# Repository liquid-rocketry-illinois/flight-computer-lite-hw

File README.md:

# Flight Computer Lite "Digital Tripper"
KiCad PCB repository for "Digital Tripper": a flight computer with no physical outputs designed for uncontrolled solid-fuel excursion flights (the first of which is planned for 2024-11), and a precursor for future flight computers that will incorporate actuation or active control or interact with other boards. The data it gathers will be used for verification of flight control and position estimation algorithms, flight vehicle design iteration, building up a strong avionics software backbone, and field-testing our electronic components and designs. Digital Tripper is a square 65mm on edge and fits transversely in a 4-inch-diameter model rocket.

Ingredients:
* The "brain", a Raspberry Pi Silicon RP2040
* Various digital sensors
    * TDK InvenSense ICM-42688-P high-accuracy 6DoF IMU
    * Bosch BMI088 6DoF IMU for backup and a higher (24 g) acceleration limit
    * STmicroelectronics LIS3MDL 3-axis magnetometer
    * TE Connectivity MS5611 barometer/altimeter
    * Sensirion SHT40 for ambient temperature and humidity
    * u-blox MAX-M10S GNSS receiver with u.FL antenna
* A push-push microSD card slot for vibration-resistant datalogging
* A piezoelectric buzzer to provide audial status information before launch and after landing
* a USB-C port for programming and serial communication with the RP2040
* A JST-PH battery connector
* Power monitor IC to characterize necessary battery size
* A 3.3V-output switching DC-DC converter

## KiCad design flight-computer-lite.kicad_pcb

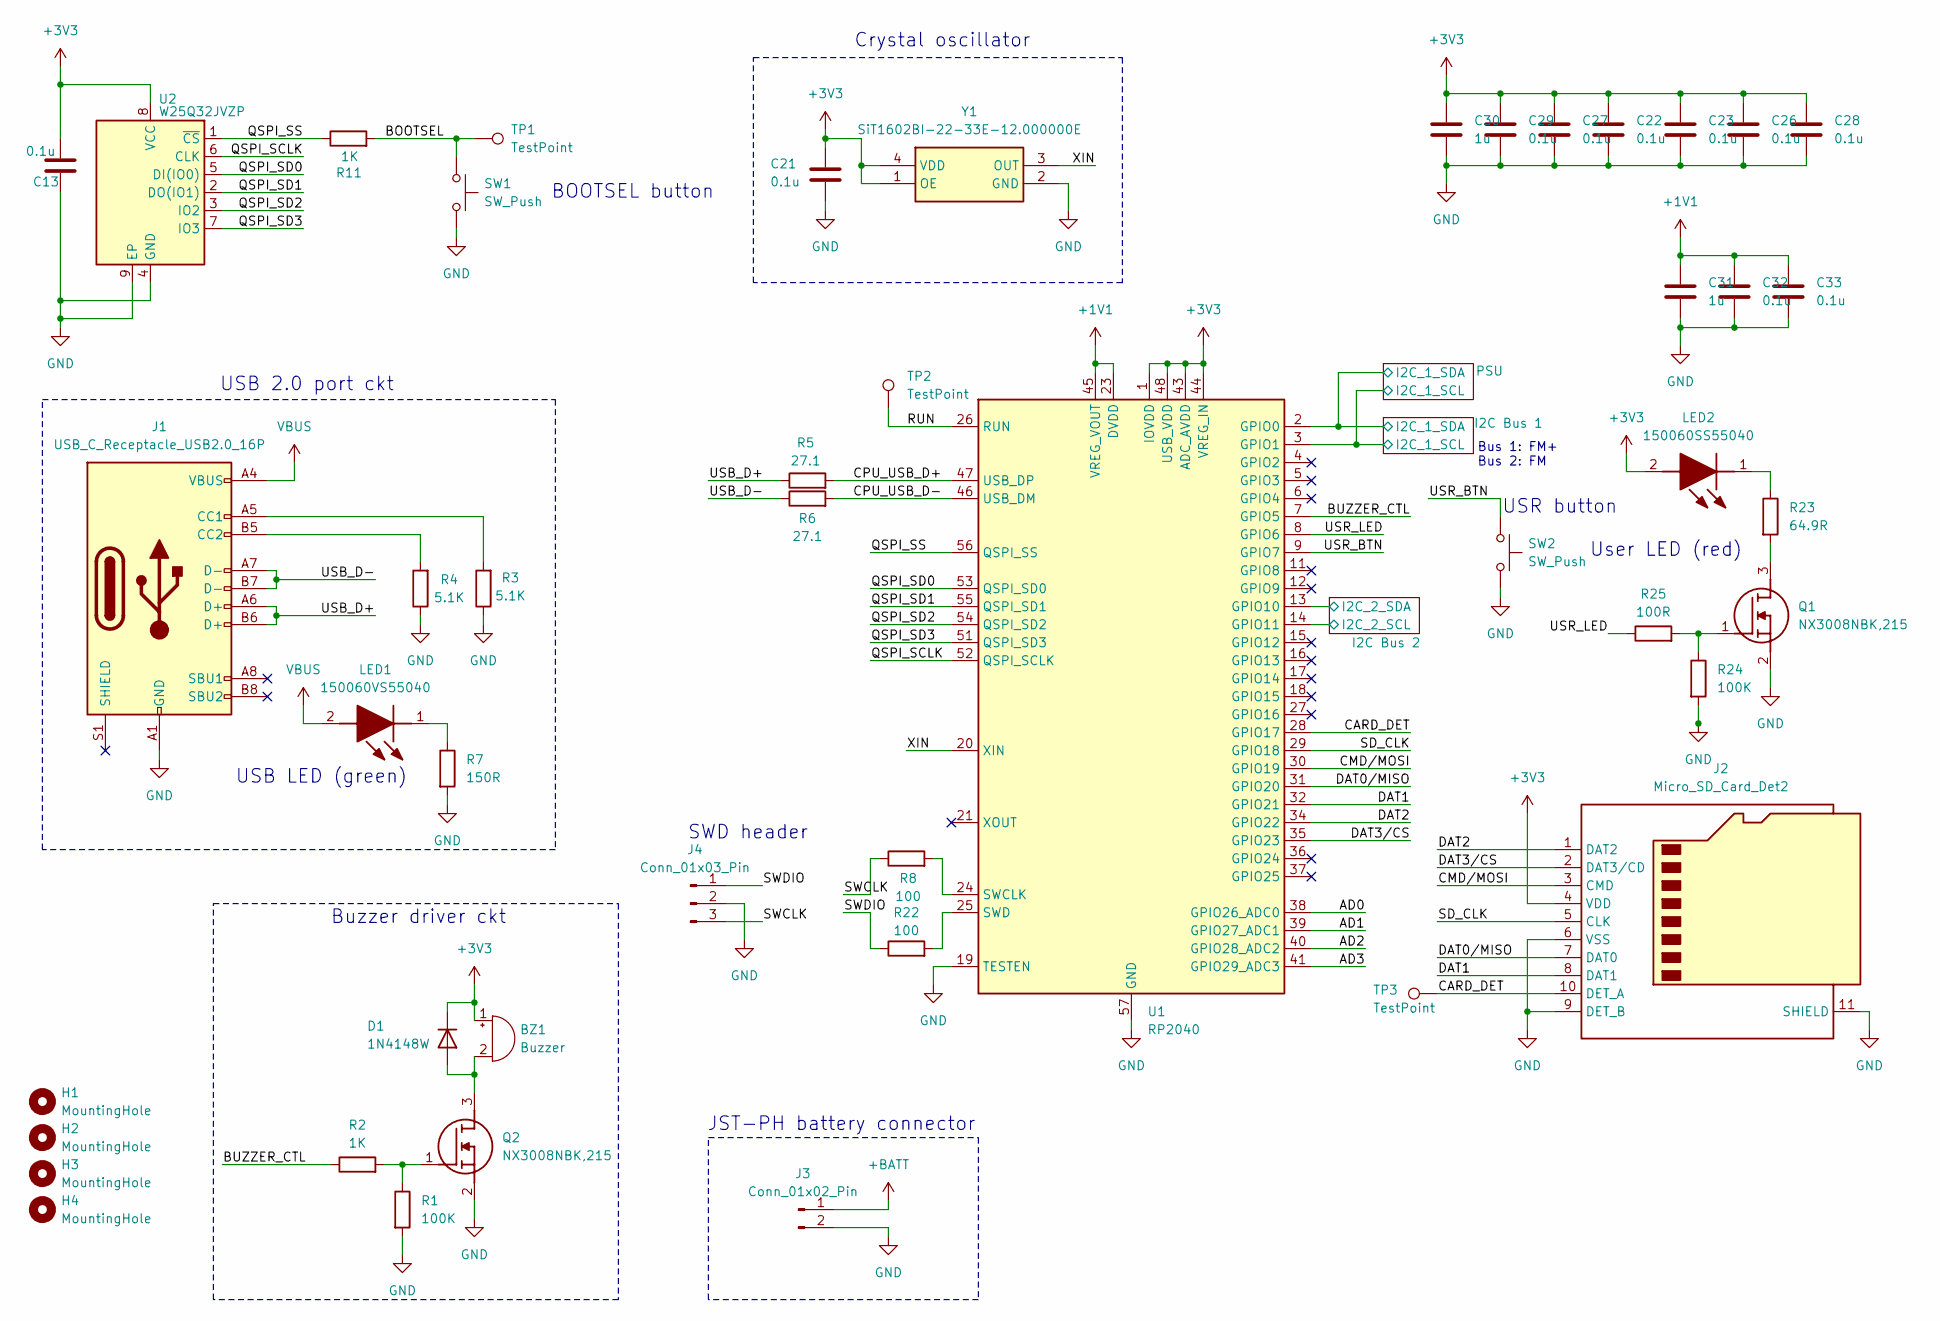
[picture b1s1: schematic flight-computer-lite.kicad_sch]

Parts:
BZ1: Buzzer; MagneticBuzzer_PUI_SMT-1028-T-2-R
C13, C21, C22, C23, C26, C27, C28, C29, C32, C33: 0.1u; C_0603_1608Metric
C30, C31: 1u; C_0603_1608Metric
D1: 1N4148W; D_SOD-323F
H1, H2, H3, H4: MountingHole; MountingHole_4.3mm_M4
J1: USB_C_Receptacle_USB2.0_16P; USB_C_Receptacle_GCT_USB4110
J2: Micro_SD_Card_Det2; microSD_HC_Hirose_DM3AT-SF-PEJM5
J3: Conn_01x02_Pin; JST_PH_S2B-PH-SM4-TB_1x02-1MP_P2.00mm_Horizontal
J4: Conn_01x03_Pin; JST_SH_BM03B-SRSS-TB_1x03-1MP_P1.00mm_Vertical
LED1: 150060VS55040; LEDM168X50N; Mouser Part Number 710-150060VS55040
LED2: 150060SS55040; Mouser Part Number 710-150060SS55040
Q1, Q2: NX3008NBK,215; NX3008NBK215; Mouser Part Number 771-NX3008NBK,215
R1, R24: 100K; R_0603_1608Metric
R2, R11: 1K; R_0603_1608Metric
R3, R4: 5.1K; R_0603_1608Metric
R5, R6: 27.1; R_0603_1608Metric
R7: 150R; R_0603_1608Metric
R8, R22: 100; R_0603_1608Metric
R23: 64.9R; R_0603_1608Metric
R25: 100R; R_0603_1608Metric
SW1, SW2: SW_Push; SW_Push_1P1T_NO_Vertical_Wuerth_434133025816
TP1, TP2, TP3: TestPoint; TestPoint_Pad_D1.0mm
U1: RP2040; QFN-56-1EP_7x7mm_P0.4mm_EP3.2x3.2mm
U2: W25Q32JVZP; WSON-8-1EP_6x5mm_P1.27mm_EP3.4x4.3mm
Y1: SiT1602BI-22-33E-12.000000E; SIT1602BI2233E12000000G; Manufacturer_Part_Number SiT1602BI-22-33E-12.000000E; Mouser Part Number N/A

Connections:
+1V1: C31.1, C32.1, C33.1, U1.23 (DVDD), U1.45 (VREG_VOUT), U1.50 (DVDD)
+3V3: BZ1.1 (+), C13.1, C21.1, C22.1, C23.1, C26.1, C27.1, C28.1, C29.1, C30.1, D1.1 (K), J2.4 (VDD), LED2.2 (A), U1.1 (IOVDD), U1.10 (IOVDD), U1.22 (IOVDD), U1.33 (IOVDD), U1.42 (IOVDD), U1.43 (ADC_AVDD), U1.44 (VREG_IN), U1.48 (USB_VDD), U1.49 (IOVDD), U2.8 (VCC), Y1.1 (OE), Y1.4 (VDD); also elsewhere on the board
+BATT: J3.1; also elsewhere on the board
/AD0: U1.38 (GPIO26_ADC0)
/AD1: U1.39 (GPIO27_ADC1)
/AD2: U1.40 (GPIO28_ADC2)
/AD3: U1.41 (GPIO29_ADC3)
/BOOTSEL: R11.2, SW1.1, TP1.1
/BUZZER_CTL: R2.1, U1.7 (GPIO5)
/CARD_DET: J2.10 (DET_A), TP3.1, U1.28 (GPIO17)
/CMD/MOSI: J2.3 (CMD), U1.30 (GPIO19)
/CPU_USB_D+: R5.2, U1.47 (USB_DP)
/CPU_USB_D-: R6.2, U1.46 (USB_DM)
/DAT0/MISO: J2.7 (DAT0), U1.31 (GPIO20)
/DAT1: J2.8 (DAT1), U1.32 (GPIO21)
/DAT2: J2.1 (DAT2), U1.34 (GPIO22)
/DAT3/CS: J2.2 (DAT3/CD), U1.35 (GPIO23)
/I2C Bus 1/I2C_1_SCL: U1.3 (GPIO1); also elsewhere on the board
/I2C Bus 1/I2C_1_SDA: U1.2 (GPIO0); also elsewhere on the board
/I2C Bus 2/I2C_2_SCL: U1.14 (GPIO11); also elsewhere on the board
/I2C Bus 2/I2C_2_SDA: U1.13 (GPIO10); also elsewhere on the board
/QSPI_SCLK: U1.52 (QSPI_SCLK), U2.6 (CLK)
/QSPI_SD0: U1.53 (QSPI_SD0), U2.5 (DI(IO0))
/QSPI_SD1: U1.55 (QSPI_SD1), U2.2 (DO(IO1))
/QSPI_SD2: U1.54 (QSPI_SD2), U2.3 (IO2)
/QSPI_SD3: U1.51 (QSPI_SD3), U2.7 (IO3)
/QSPI_SS: R11.1, U1.56 (QSPI_SS), U2.1 (~CS)
/RUN: TP2.1, U1.26 (RUN)
/SD_CLK: J2.5 (CLK), U1.29 (GPIO18)
/SWCLK: J4.3, R8.1
/SWDIO: J4.1, R22.1
/USB_D+: J1.A6 (D+), J1.B6 (D+), R5.1
/USB_D-: J1.A7 (D-), J1.B7 (D-), R6.1
/USR_BTN: SW2.1, U1.9 (GPIO7)
/USR_LED: R25.1, U1.8 (GPIO6)
/XIN: U1.20 (XIN), Y1.3 (OUT)
GND: C13.2, C21.2, C22.2, C23.2, C26.2, C27.2, C28.2, C29.2, C30.2, C31.2, C32.2, C33.2, J1.A1 (GND), J1.A12 (GND), J1.B1 (GND), J1.B12 (GND), J2.6 (VSS), J2.9 (DET_B), J2.11 (SHIELD), J3.2, J4.2, J4.MP, Q1.2 (S), Q2.2 (S), R1.2, R3.1, R4.1, R7.2, R24.2, SW1.2, SW2.2, U1.19 (TESTEN), U1.57 (GND), U2.4 (GND), U2.9 (EP), Y1.2 (GND); also elsewhere on the board
unnamed: BZ1.2 (-), D1.2 (A), Q2.3 (D)
unnamed: J1.A5 (CC1), R3.2
unnamed: J1.B5 (CC2), R4.2
unnamed: LED1.1 (K), R7.1
unnamed: LED2.1 (K), R23.1
unnamed: Q1.3 (D), R23.2
unnamed: Q1.1 (G), R24.1, R25.2
unnamed: Q2.1 (G), R1.1, R2.2
unnamed: R8.2, U1.24 (SWCLK)
unnamed: R22.2, U1.25 (SWD)
VBUS: J1.A4 (VBUS), J1.A9 (VBUS), J1.B4 (VBUS), J1.B9 (VBUS), LED1.2 (A); also elsewhere on the board

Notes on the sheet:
Bus 1: FM+ Bus 2: FM
Buzzer driver ckt
JST-PH battery connector
BOOTSEL button
User LED (red)
SWD header
USB LED (green)
USR button
Crystal oscillator
USB 2.0 port ckt

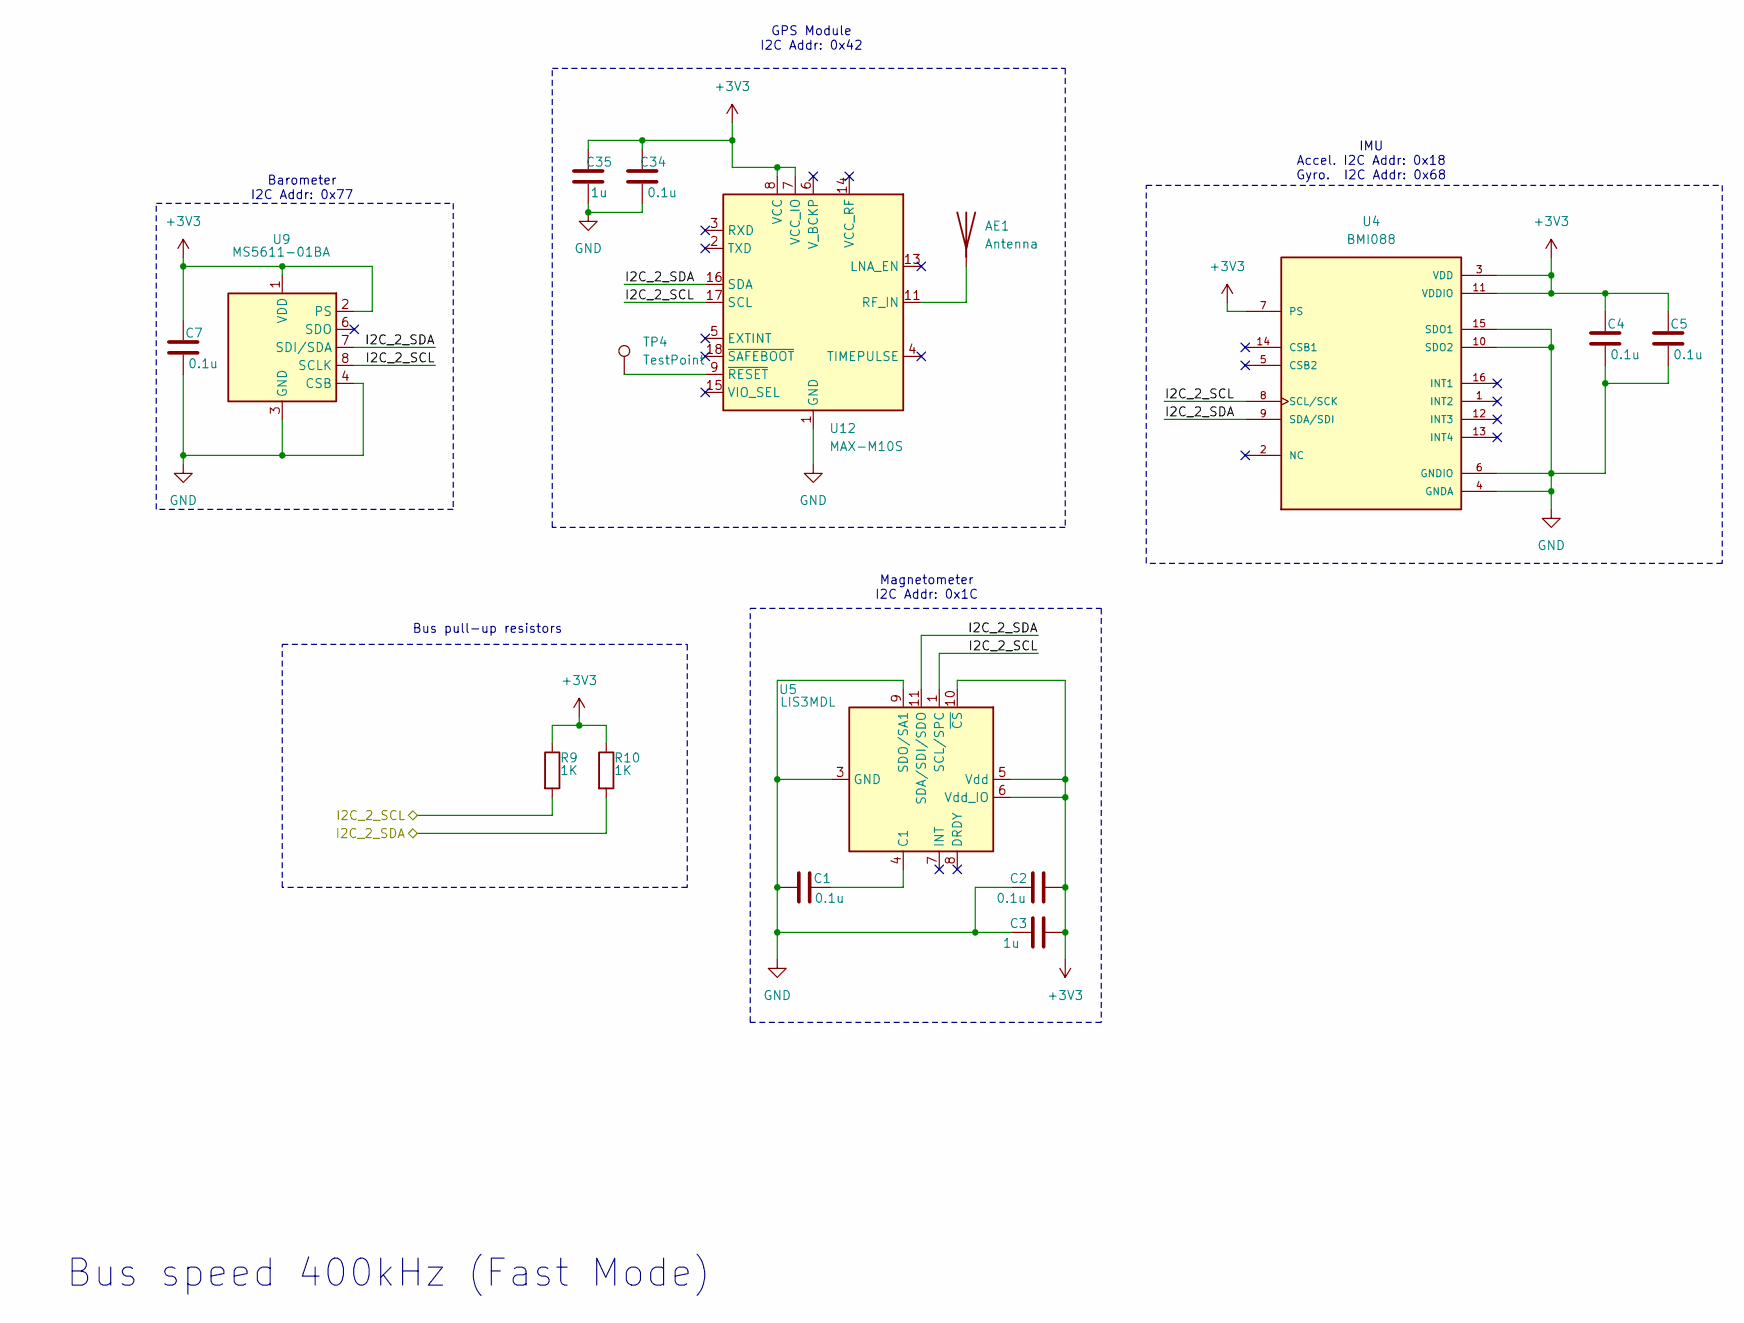
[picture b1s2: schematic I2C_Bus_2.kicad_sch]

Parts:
AE1: Antenna; U.FL_Hirose_U.FL-R-SMT-1_Vertical
C1, C2, C4, C5, C7, C34: 0.1u; C_0603_1608Metric
C3, C35: 1u; C_0603_1608Metric
R9, R10: 1K; R_0603_1608Metric
TP4: TestPoint; TestPoint_Pad_D1.0mm
U4: BMI088; PQFN50P450X300X100-16N
U5: LIS3MDL; LGA-12_2x2mm_P0.5mm
U9: MS5611-01BA; LGA-8_3x5mm_P1.25mm
U12: MAX-M10S; ublox_MAX

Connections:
+3V3: C2.2, C3.2, C4.2, C5.2, C7.2, C34.2, C35.2, R9.1, R10.1, U4.3 (VDD), U4.7 (PS), U4.11 (VDDIO), U5.5 (Vdd), U5.6 (Vdd_IO), U5.10 (~CS), U9.1 (VDD), U9.2 (PS), U12.7 (VCC_IO), U12.8 (VCC); also elsewhere on the board
/I2C Bus 2/I2C_2_SCL: R9.2, U4.8 (SCL/SCK), U5.1 (SCL/SPC), U9.8 (SCLK), U12.17 (SCL); also elsewhere on the board
/I2C Bus 2/I2C_2_SDA: R10.2, U4.9 (SDA/SDI), U5.11 (SDA/SDI/SDO), U9.7 (SDI/SDA), U12.16 (SDA); also elsewhere on the board
GND: AE1.2, C1.1, C2.1, C3.1, C4.1, C5.1, C7.1, C34.1, C35.1, U4.4 (GNDA), U4.6 (GNDIO), U4.10 (SDO2), U4.15 (SDO1), U5.2 (GND), U5.3 (GND), U5.9 (SDO/SA1), U5.12 (GND), U9.3 (GND), U9.4 (CSB), U9.5 (CSB), U12.1 (GND), U12.10 (GND), U12.12 (GND); also elsewhere on the board
unnamed: AE1.1 (A), U12.11 (RF_IN)
unnamed: C1.2, U5.4 (C1)
unnamed: TP4.1, U12.9 (~RESET)

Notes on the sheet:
Magnetometer I2C Addr: 0x1C
IMU Accel. I2C Addr: 0x18 Gyro. I2C Addr: 0x68
GPS Module I2C Addr: 0x42
Bus pull-up resistors
Bus speed 400kHz (Fast Mode)
Barometer I2C Addr: 0x77

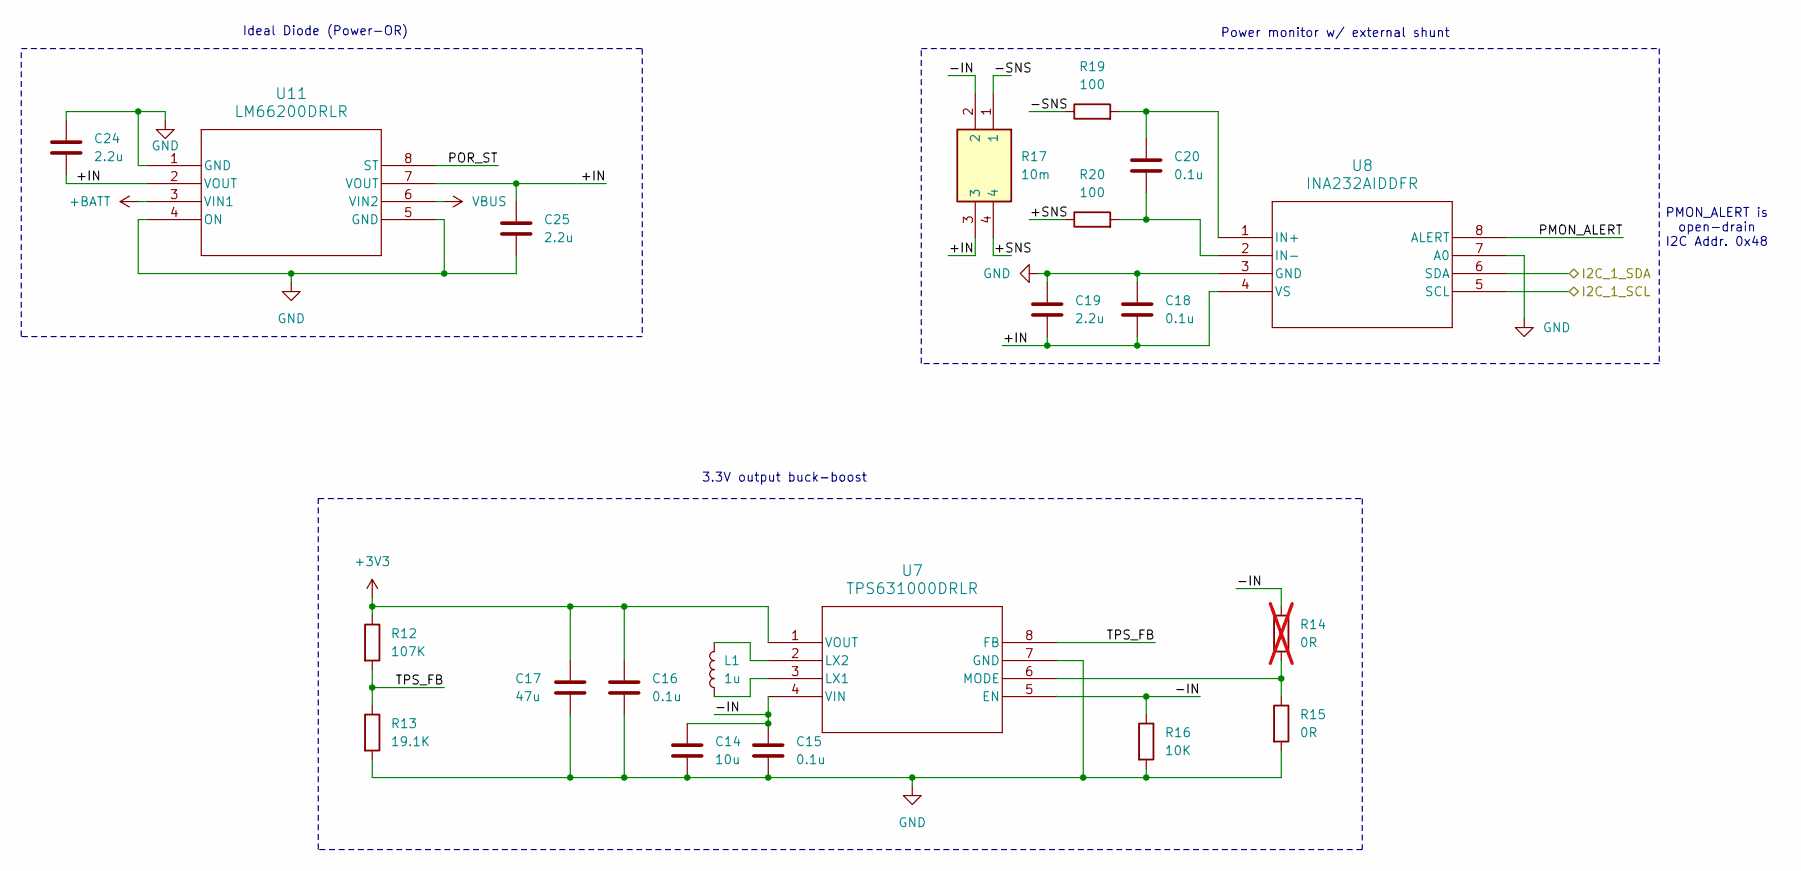
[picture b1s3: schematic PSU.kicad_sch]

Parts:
C14: 10u; C_0603_1608Metric
C15, C16, C18, C20: 0.1u; C_0603_1608Metric
C17: 47u; C_0805_2012Metric
C19, C24, C25: 2.2u; C_0603_1608Metric
L1: 1u; L_1008_2520Metric
R12: 107K; R_0603_1608Metric
R13: 19.1K; R_0603_1608Metric
R14: 0R; R_0603_1608Metric; not fitted
R15: 0R; R_0603_1608Metric
R16: 10K; R_0603_1608Metric
R17: 10m; L4CA0612L0M50FNR; Manufacturer_Part_Number L4CA0612LR010FNR
R19, R20: 100; R_0603_1608Metric
U7: TPS631000DRLR; TPS631000DRLR_TEX
U8: INA232AIDDFR
U11: LM66200DRLR; LM66200

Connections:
+3V3: C16.1, C17.1, R12.1, U7.1 (VOUT); also elsewhere on the board
+BATT: U11.3 (VIN1); also elsewhere on the board
/I2C Bus 1/I2C_1_SCL: U8.5 (SCL); also elsewhere on the board
/I2C Bus 1/I2C_1_SDA: U8.6 (SDA); also elsewhere on the board
/PSU/+IN: C18.2, C19.2, C24.2, C25.1, R17.3, U8.4 (VS), U11.2 (VOUT), U11.7 (VOUT)
/PSU/+SNS: R17.4, R20.1
/PSU/-IN: C14.1, C15.1, R14.1, R16.1, R17.2, U7.4 (VIN), U7.5 (EN)
/PSU/-SNS: R17.1, R19.1
/PSU/PMON_ALERT: U8.8 (ALERT)
/PSU/POR_ST: U11.8 (ST)
/PSU/TPS_FB: R12.2, R13.1, U7.8 (FB)
GND: C14.2, C15.2, C16.2, C17.2, C18.1, C19.1, C24.1, C25.2, R13.2, R15.2, R16.2, U7.7 (GND), U8.3 (GND), U8.7 (A0), U11.1 (GND), U11.4 (ON), U11.5 (GND); also elsewhere on the board
unnamed: L1.1, U7.3 (LX1)
unnamed: L1.2, U7.2 (LX2)
unnamed: R14.2, R15.1, U7.6 (MODE)
unnamed: C20.1, R19.2, U8.1 (IN+)
unnamed: C20.2, R20.2, U8.2 (IN-)
VBUS: U11.6 (VIN2); also elsewhere on the board

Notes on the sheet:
Power monitor w/ external shunt
PMON_ALERT is open-drain I2C Addr. 0x48
3.3V output buck-boost
Ideal Diode (Power-OR)

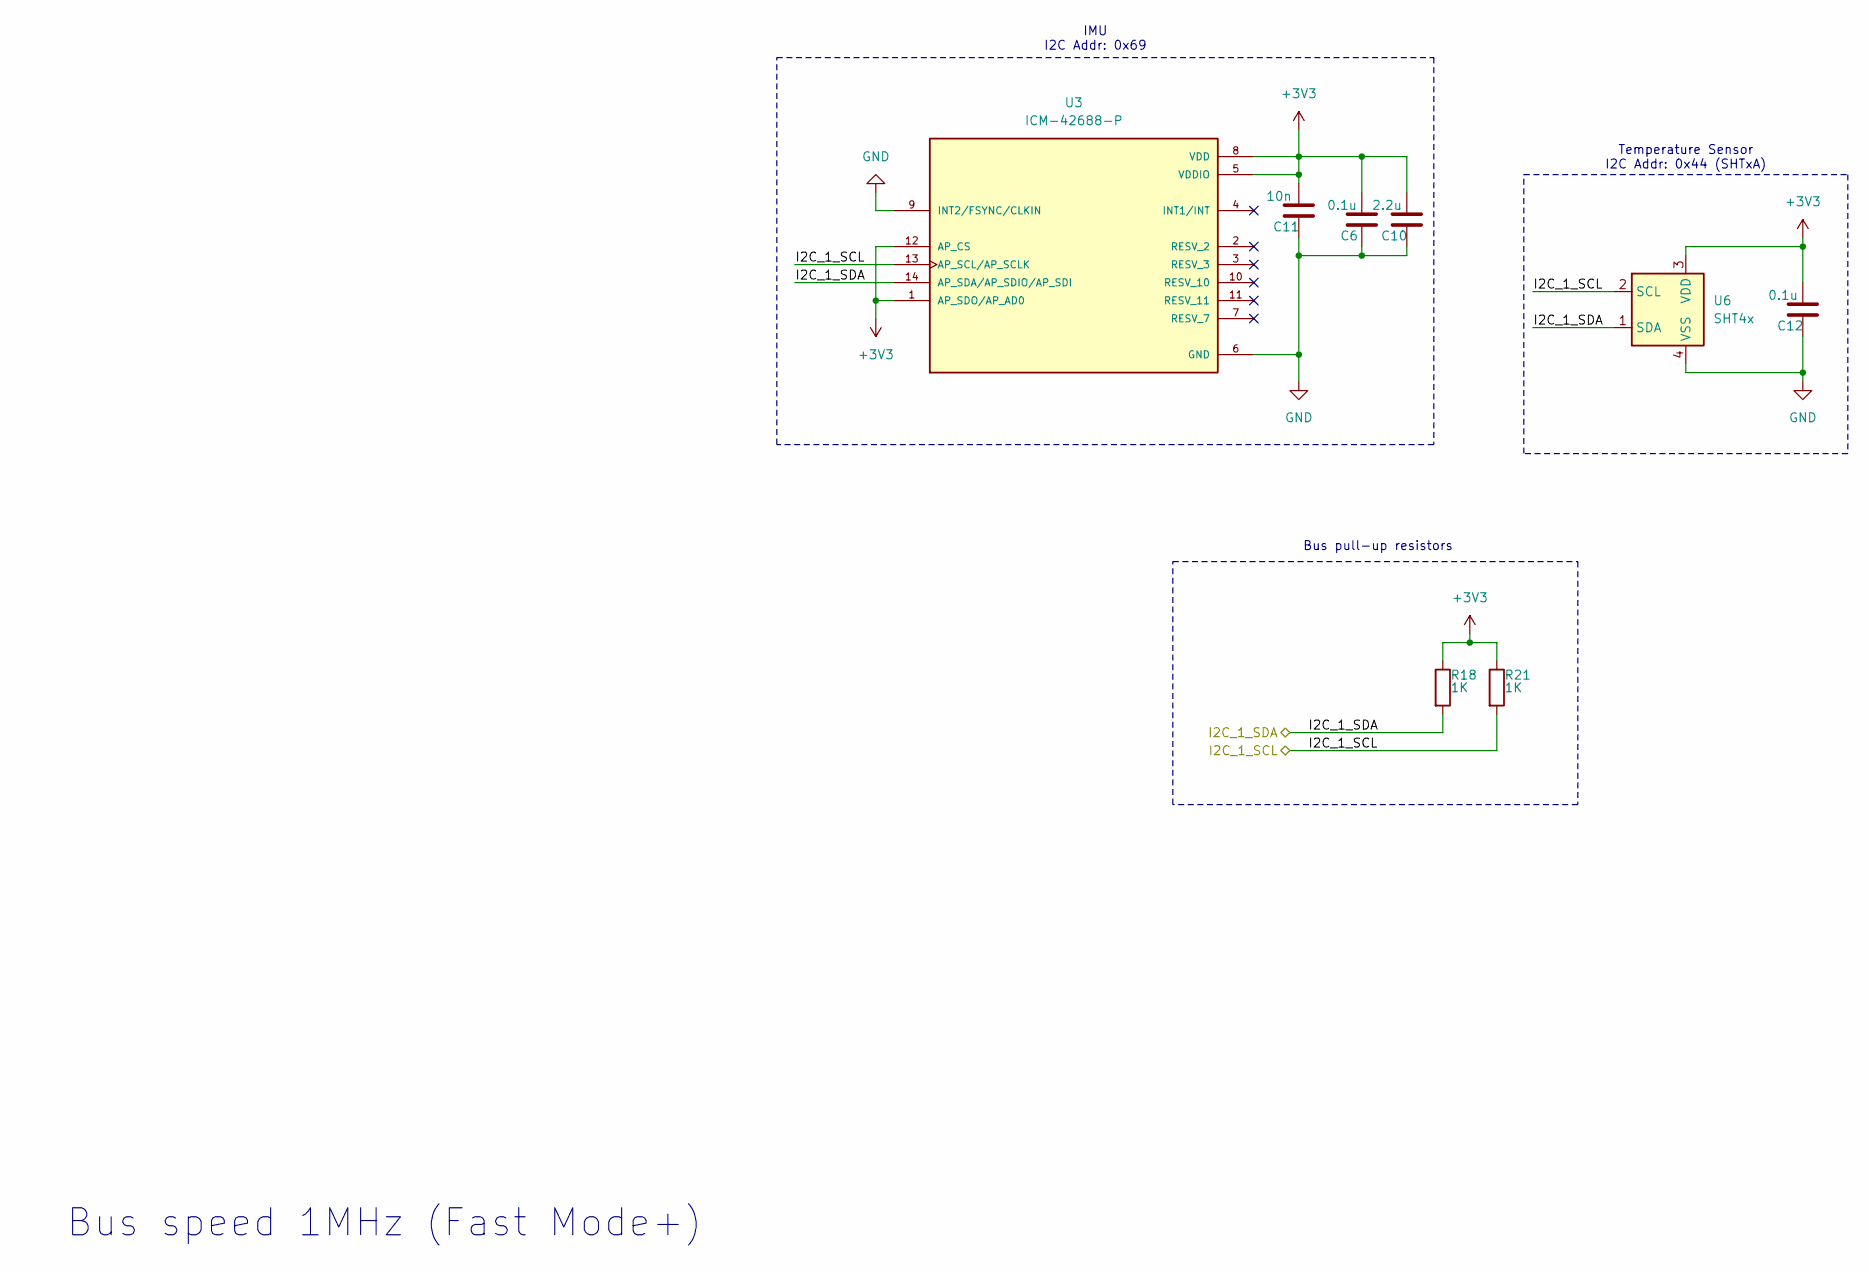
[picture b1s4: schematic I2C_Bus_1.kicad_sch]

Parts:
C6, C12: 0.1u; C_0603_1608Metric
C10: 2.2u; C_0603_1608Metric
C11: 10n; C_0603_1608Metric
R18, R21: 1K; R_0603_1608Metric
U3: ICM-42688-P; PQFN50P300X250X97-14N; PARTREV 1.2
U6: SHT4x; Sensirion_DFN-4_1.5x1.5mm_P0.8mm_SHT4x_NoCentralPad

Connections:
+3V3: C6.2, C10.2, C11.2, C12.2, R18.1, R21.1, U3.1 (AP_SDO/AP_AD0), U3.5 (VDDIO), U3.8 (VDD), U3.12 (AP_CS), U6.3 (VDD); also elsewhere on the board
/I2C Bus 1/I2C_1_SCL: R21.2, U3.13 (AP_SCL/AP_SCLK), U6.2 (SCL); also elsewhere on the board
/I2C Bus 1/I2C_1_SDA: R18.2, U3.14 (AP_SDA/AP_SDIO/AP_SDI), U6.1 (SDA); also elsewhere on the board
GND: C6.1, C10.1, C11.1, C12.1, U3.6 (GND), U3.9 (INT2/FSYNC/CLKIN), U6.4 (VSS); also elsewhere on the board

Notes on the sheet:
Temperature Sensor I2C Addr: 0x44 (SHTxA)
IMU I2C Addr: 0x69
Bus speed 1MHz (Fast Mode+)
Bus pull-up resistors

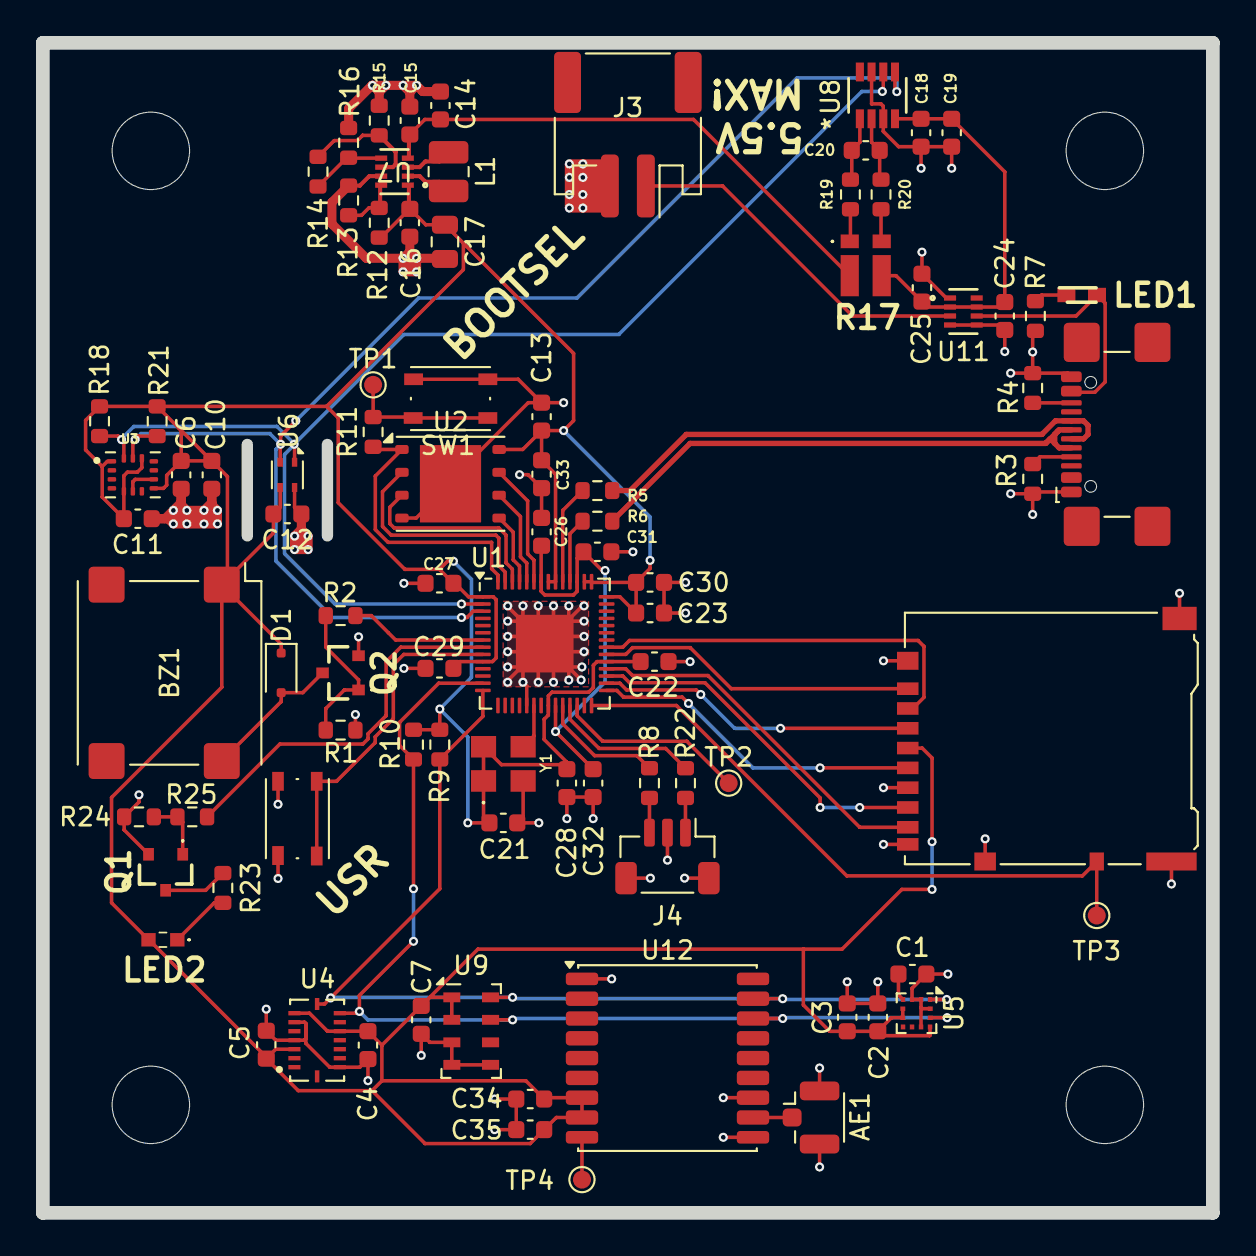
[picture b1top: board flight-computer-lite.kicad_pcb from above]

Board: 2 copper layers, 65.0 x 65.0 mm, 92 parts (0 on the bottom side), 57 nets.

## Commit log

2024-09-09 README
2024-09-10 Initial commit of KiCad files
2024-09-10 Added mounting holes
2024-09-10 Changed board surface finish, added GPS
2024-09-11 replaced nrnd BME680 with HDC2080
2024-09-12 Changed buzzer partno
2024-09-22 Created LRI_partlib
    Created a local part library for the project (that can be reused on others in the future).
    Added the ICM-42688-P and BMI088 IMUs to it.
    Added them to the PCB and reorganized some things.
2024-09-23 Added battery, updated USB
2024-09-24 Added I2C Devices
2024-09-24 Changed Battery Connector Footprint
2024-09-24 Wired flash
2024-09-30 Added buck-boost
2024-10-02 Finished PSU
2024-10-07 Added buttons, LEDs, TPs, and Miku
2024-10-07 Added more decoupling caps
2024-10-07 Added more 3d models and rearranged layout
2024-10-08 Tentatively finished schematic
2024-10-08 Added I2C resistor values
2024-10-09 Moved LIS3MDL to FM bus
2024-10-12 Changed out GPS module
2024-10-12 Added 3D model for MAX-M10S and adjusted footprint
2024-10-12 Changed FM I2C bus pins
2024-10-12 oops wrong pins
2024-10-12 Fixed hierarchy pins in I2C 1 bus schematic
2024-10-12 Adjusted VREG IN/OUT Decoupling capacitor values to match datasheet suggestion
2024-10-12 Changed USR_LED and USR_BTN pins
2024-10-12 oops wrong pin again
2024-10-14 WIP layout/route
2024-10-19 Routed PSU
2024-10-20 Adjusted footprints for LIS3MDL and BMI088
2024-10-21 Adjusted ICM42688 footprint
2024-10-21 Adjusted LM66200 pcb
2024-10-22 major routing update!
2024-10-22 Moved pin numbers on remaining parts
2024-10-23 Fixed PSU, routed
2024-10-24 Almost done with routing
2024-10-28 Silkscreen finished
2024-10-29 Fixed slots
2024-10-29 Moved back silkscreen
2024-10-30 Design complete (hopefully)
2024-11-04 Done
2025-03-11 Schematic exported to PDF
2025-04-17 added pictures to readme
